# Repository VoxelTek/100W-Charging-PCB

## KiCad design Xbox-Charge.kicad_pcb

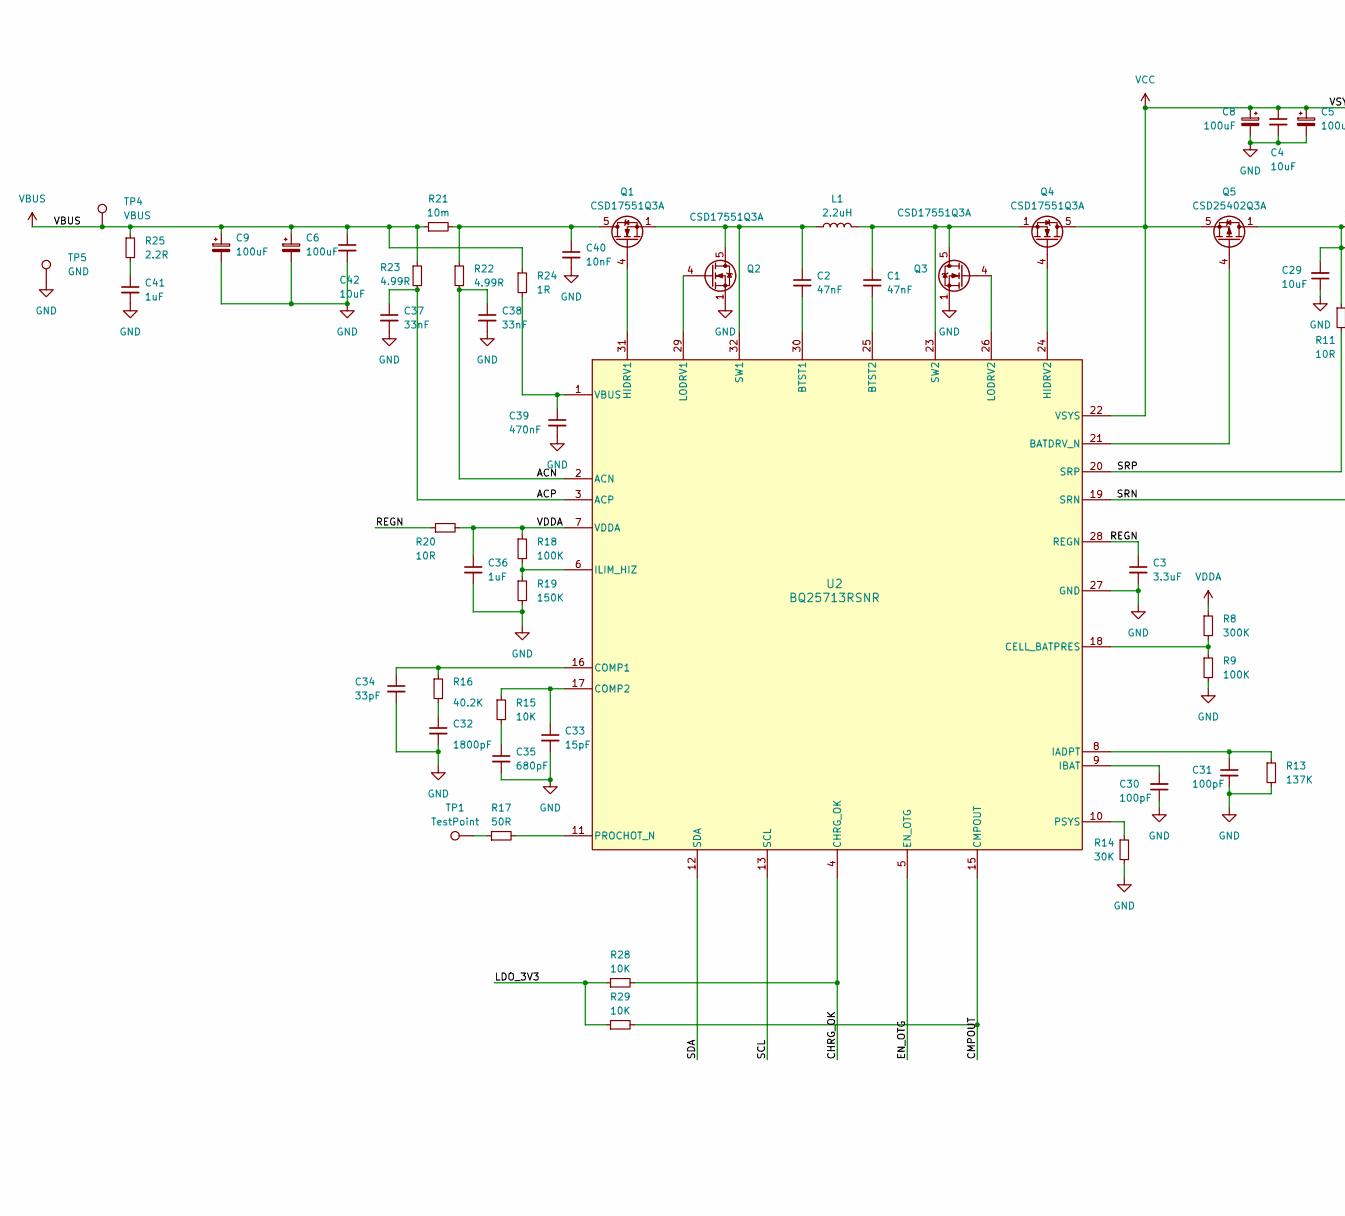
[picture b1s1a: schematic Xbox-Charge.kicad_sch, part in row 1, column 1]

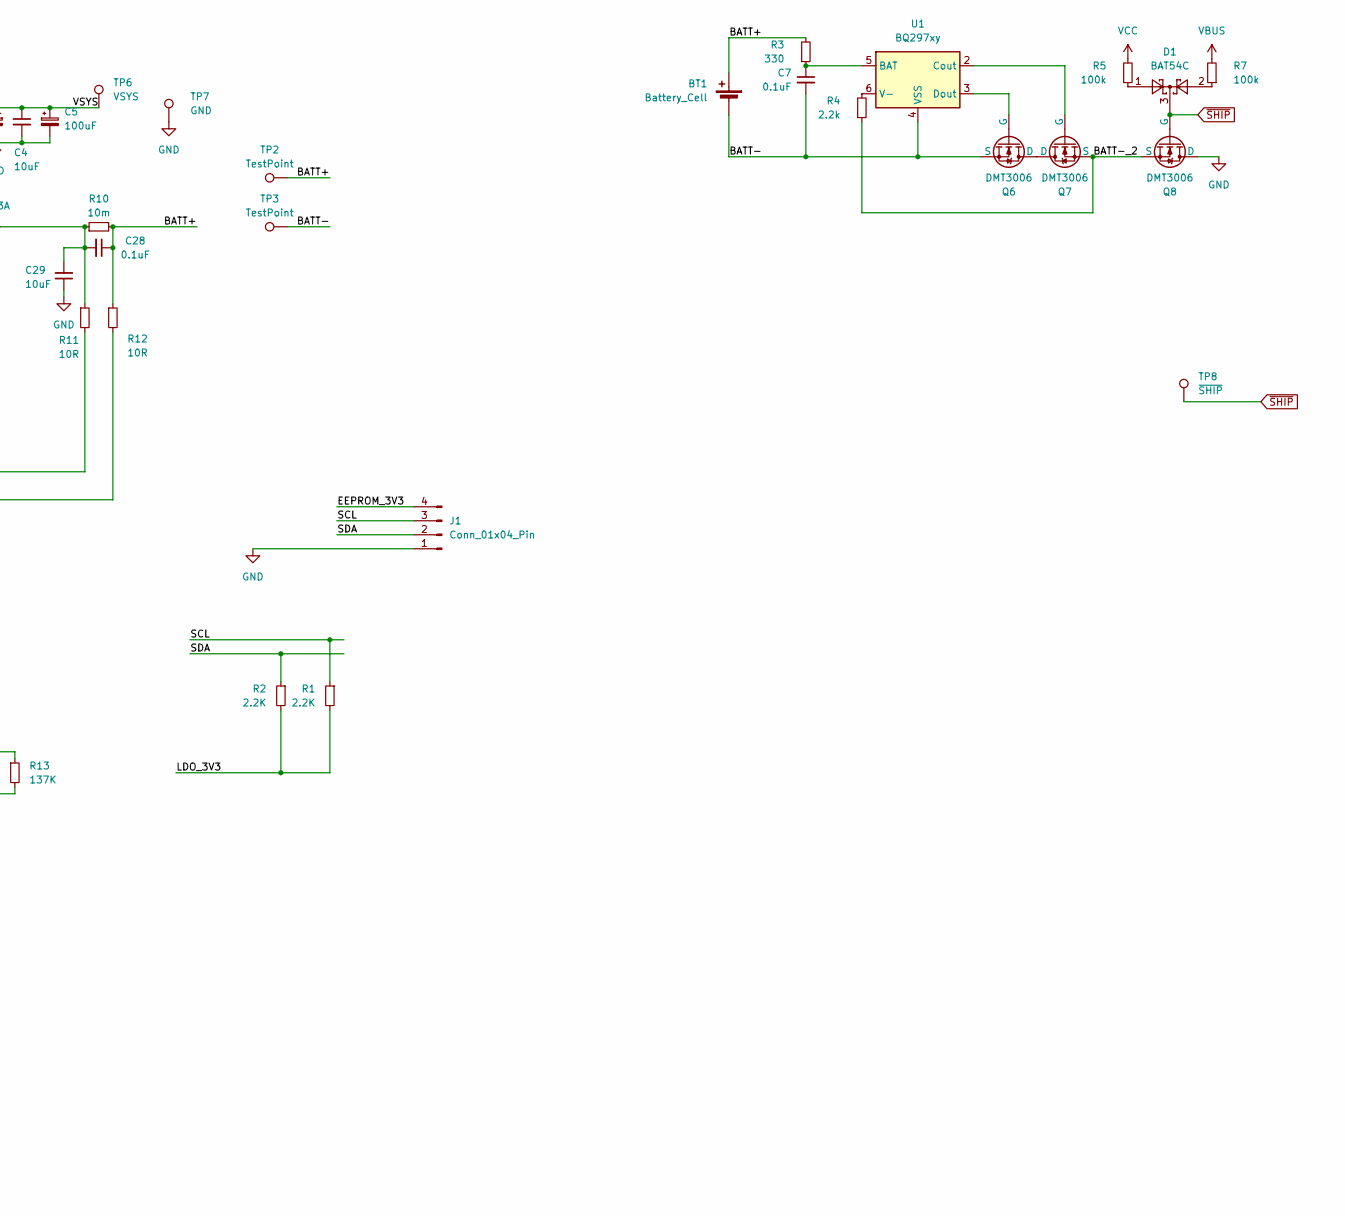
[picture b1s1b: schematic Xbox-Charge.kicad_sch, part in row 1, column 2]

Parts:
BT1: Battery_Cell
C1, C2: 47nF; C_0603_1608Metric
C3: 3.3uF; C_0603_1608Metric
C4, C42: 10uF; C_0805_2012Metric
C5, C6, C8, C9: 100uF; CP_EIA-3216-18_Kemet-A
C7: 0.1uF; C_0402_1005Metric
C28: 0.1uF; C_0603_1608Metric
C29: 10uF; C_0603_1608Metric
C30, C31: 100pF; C_0603_1608Metric
C32: 1800pF; C_0402_1005Metric
C33: 15pF; C_0402_1005Metric
C34: 33pF; C_0402_1005Metric
C35: 680pF; C_0402_1005Metric
C36: 1uF; C_0402_1005Metric
C37, C38: 33nF; C_0603_1608Metric
C39: 470nF; C_0805_2012Metric
C40: 10nF; C_0402_1005Metric
C41: 1uF
D1: BAT54C; SOT-23-3
J1: Conn_01x04_Pin; PROG
L1: 2.2uH; L_Chilisin_BMRx00060630
Q1, Q2, Q3, Q4: CSD17551Q3A; VSON-8_3.3x3.3mm_P0.65mm_NexFET
Q5: CSD25402Q3A; VSON-8_3.3x3.3mm_P0.65mm_NexFET
Q6, Q7, Q8: DMT3006; Diodes_UDFN2020-6_Type-F
R1, R2: 2.2K; R_0402_1005Metric
R3: 330; R_0402_1005Metric
R4: 2.2k; R_0402_1005Metric
R5, R7: 100k; R_0402_1005Metric
R8: 300K; R_0402_1005Metric
R9, R18: 100K; R_0402_1005Metric
R10, R21: 10m; R_1206_3216Metric
R11, R12: 10R; R_0603_1608Metric
R13: 137K; R_0603_1608Metric
R14: 30K; R_0603_1608Metric
R15, R28, R29: 10K; R_0402_1005Metric
R16: 40.2K; R_0402_1005Metric
R17: 50R
R19: 150K; R_0402_1005Metric
R20: 10R; R_0402_1005Metric
R22, R23: 4.99R; R_0603_1608Metric
R24: 1R; R_0805_2012Metric
R25: 2.2R
TP1: TestPoint
TP2, TP3: TestPoint; TestPoint_Pad_3.0x3.0mm
TP4: VBUS; TestPoint_Plated_Hole_D3.0mm
TP5, TP7: GND; TestPoint_Plated_Hole_D3.0mm
TP6: VSYS; TestPoint_Plated_Hole_D3.0mm
TP8: ~{SHIP}; TestPoint_Pad_D1.5mm
U1: BQ297xy; WSON-6_1.5x1.5mm_P0.5mm
U2: BQ25713RSNR; Texas_RSN_WQFN-32-1EP_4x4mm_P0.4mm_EP2.8x2.8mm

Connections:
/ACN: C38.1, R22.2, U2.2 (ACN)
/ACP: C37.1, R23.2, U2.3 (ACP)
/BATT+: BT1.1 (+), C28.1, R3.2, R10.2, R12.1, TP2.1
/BATT-: BT1.2 (-), C7.2, Q6.4 (S), Q6.8 (S), TP3.1, U1.4 (VSS)
/BATT-_2: Q7.4 (S), Q7.8 (S), Q8.4 (S), Q8.8 (S), R4.1
/CHRG_OK: R28.2, U2.4 (CHRG_OK)
/CMPOUT: R29.2, U2.15 (CMPOUT)
/EEPROM_3V3: J1.4; also elsewhere on the board
/EN_OTG: U2.5 (EN_OTG)
/LDO_3V3: R1.2, R2.2, R28.1, R29.1; also elsewhere on the board
/REGN: C3.1, R20.1, U2.28 (REGN)
/SCL: J1.3, R1.1, U2.13 (SCL)
/SDA: J1.2, R2.1, U2.12 (SDA)
/SRN: R12.2, U2.19 (SRN)
/SRP: R11.2, U2.20 (SRP)
GND: C3.2, C4.2, C5.2, C6.2, C8.2, C9.2, C29.1, C30.1, C31.2, C32.2, C33.2, C34.2, C35.2, C36.2, C37.2, C38.2, C39.2, C40.2, C41.2, C42.2, J1.1, Q2.1 (S), Q2.2 (S), Q2.3 (S), Q3.1 (S), Q3.2 (S), Q3.3 (S), Q8.1 (D), Q8.2 (D), Q8.5 (D), Q8.6 (D), Q8.7 (D), R9.2, R13.2, R14.2, R19.2, TP5.1, TP7.1, U2.27 (GND), U2.33 (PAD); also elsewhere on the board
unnamed: C28.2, C29.2, Q5.1 (D), Q5.2 (D), Q5.3 (D), R10.1, R11.1
unnamed: C32.1, R16.2
unnamed: C35.1, R15.2
unnamed: C41.1, R25.2
unnamed: D1.1, R5.1
unnamed: D1.2, R7.1
unnamed: C40.1, Q1.5 (D), R21.2, R22.1
unnamed: Q1.4 (G), U2.31 (HIDRV1)
unnamed: C2.1, L1.1, Q1.1 (S), Q1.2 (S), Q1.3 (S), Q2.5 (D), U2.32 (SW1)
unnamed: Q2.4 (G), U2.29 (LODRV1)
unnamed: C1.1, L1.2, Q3.5 (D), Q4.1 (S), Q4.2 (S), Q4.3 (S), U2.23 (SW2)
unnamed: Q3.4 (G), U2.26 (LODRV2)
unnamed: Q4.4 (G), U2.24 (HIDRV2)
unnamed: Q5.4 (G), U2.21 (BATDRV_N)
unnamed: Q6.1 (D), Q6.2 (D), Q6.5 (D), Q6.6 (D), Q6.7 (D), Q7.1 (D), Q7.2 (D), Q7.5 (D), Q7.6 (D), Q7.7 (D)
unnamed: Q6.3 (G), U1.3 (Dout)
unnamed: Q7.3 (G), U1.2 (Cout)
unnamed: R17.1, TP1.1
unnamed: C7.1, R3.1, U1.5 (BAT)
unnamed: R4.2, U1.6 (V-)
unnamed: C2.2, U2.30 (BTST1)
unnamed: C1.2, U2.25 (BTST2)
unnamed: R8.2, R9.1, U2.18 (CELL_BATPRES)
unnamed: C34.1, R16.1, U2.16 (COMP1)
unnamed: C33.1, R15.1, U2.17 (COMP2)
unnamed: C31.1, R13.1, U2.8 (IADPT)
unnamed: C30.2, U2.9 (IBAT)
unnamed: R18.2, R19.1, U2.6 (ILIM_HIZ)
unnamed: R17.2, U2.11 (PROCHOT_N)
unnamed: R14.1, U2.10 (PSYS)
unnamed: C39.1, R24.2, U2.1 (VBUS)
VBUS: C6.1, C9.1, C42.1, R7.2, R21.1, R23.1, R24.1, R25.1, TP4.1; also elsewhere on the board
VCC: C4.1, C5.1, C8.1, Q4.5 (D), Q5.5 (S), R5.2, TP6.1, U2.22 (VSYS)
VDDA: C36.1, R8.1, R18.1, R20.2, U2.7 (VDDA)
~SHIP: D1.3, Q8.3 (G), TP8.1

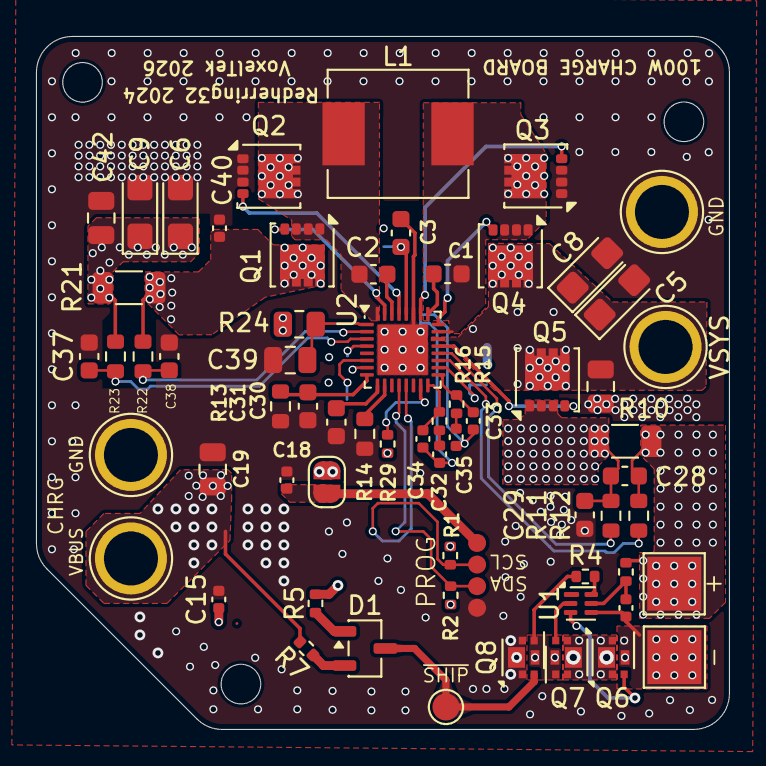
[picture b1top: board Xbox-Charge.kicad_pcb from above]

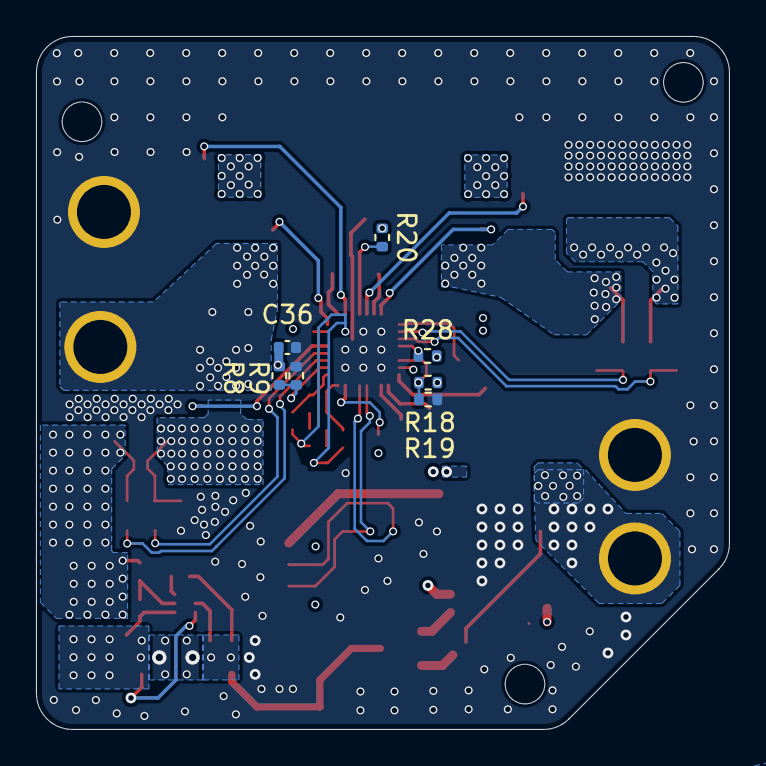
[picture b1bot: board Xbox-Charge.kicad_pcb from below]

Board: 4 copper layers, 38.5 x 38.5 mm, 71 parts (7 on the bottom side), 47 nets.

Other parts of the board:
C15: 10uF; C_0402_1005Metric
C18: 0.1uF; C_0402_1005Metric
C19: 4.7uF; C_0805_2012Metric
JP1: Jumper_2_Open; SolderJumper-2_P1.3mm_Open_RoundedPad1.0x1.5mm

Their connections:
/EEPROM_3V3: C18.1, JP1.1 (A); also elsewhere on the board
/LDO_3V3: C15.1, JP1.2 (B); also elsewhere on the board
GND: C15.2, C18.2, C19.2; also elsewhere on the board
VBUS: C19.1; also elsewhere on the board

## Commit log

2025-05-14 misc
2025-05-16 Slight changes, may need to largely redesign
2025-05-18 Remove USB-C controller, planning to use MelonHD
2025-05-28 Trim corner
2026-04-21 Rework 100W charge PCB, begin adding protection
2026-06-07 misc improvements
